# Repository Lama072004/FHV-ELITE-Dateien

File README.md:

# FHV-ELITE
 
Alle Dateien vom Elektronik und Informationstechnologie Studium

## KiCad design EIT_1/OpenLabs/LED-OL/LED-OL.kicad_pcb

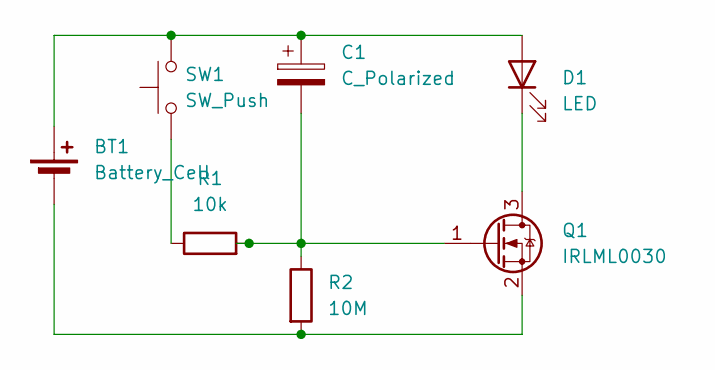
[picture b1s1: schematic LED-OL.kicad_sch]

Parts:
BT1: Battery_Cell; BatteryHolder_Multicomp_BC-2001_1x2032
C1: C_Polarized; C_0603_1608Metric
D1: LED; LED_D1.8mm_W3.3mm_H2.4mm
Q1: IRLML0030; SOT-23
R1: 10k; R_0603_1608Metric
R2: 10M; R_0603_1608Metric
SW1: SW_Push; SW_Push_SPST_NO_Alps_SKRK

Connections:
unnamed: BT1.1 (+), C1.1, D1.2 (A), SW1.2
unnamed: BT1.2 (-), Q1.2 (S), R2.2
unnamed: D1.1 (K), Q1.3 (D)
unnamed: C1.2, Q1.1 (G), R1.2, R2.1
unnamed: R1.1, SW1.1

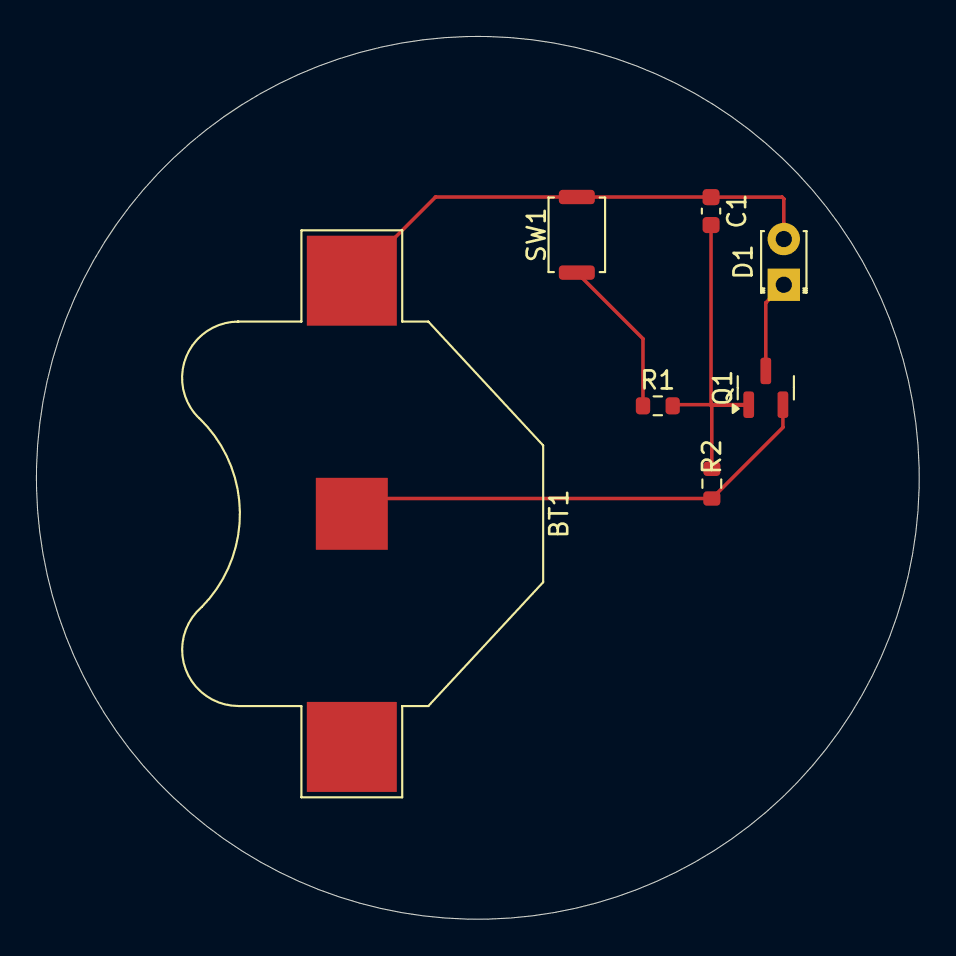
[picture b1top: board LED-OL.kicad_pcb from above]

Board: 2 copper layers, 49.0 x 49.0 mm, 7 parts (0 on the bottom side), 5 nets.

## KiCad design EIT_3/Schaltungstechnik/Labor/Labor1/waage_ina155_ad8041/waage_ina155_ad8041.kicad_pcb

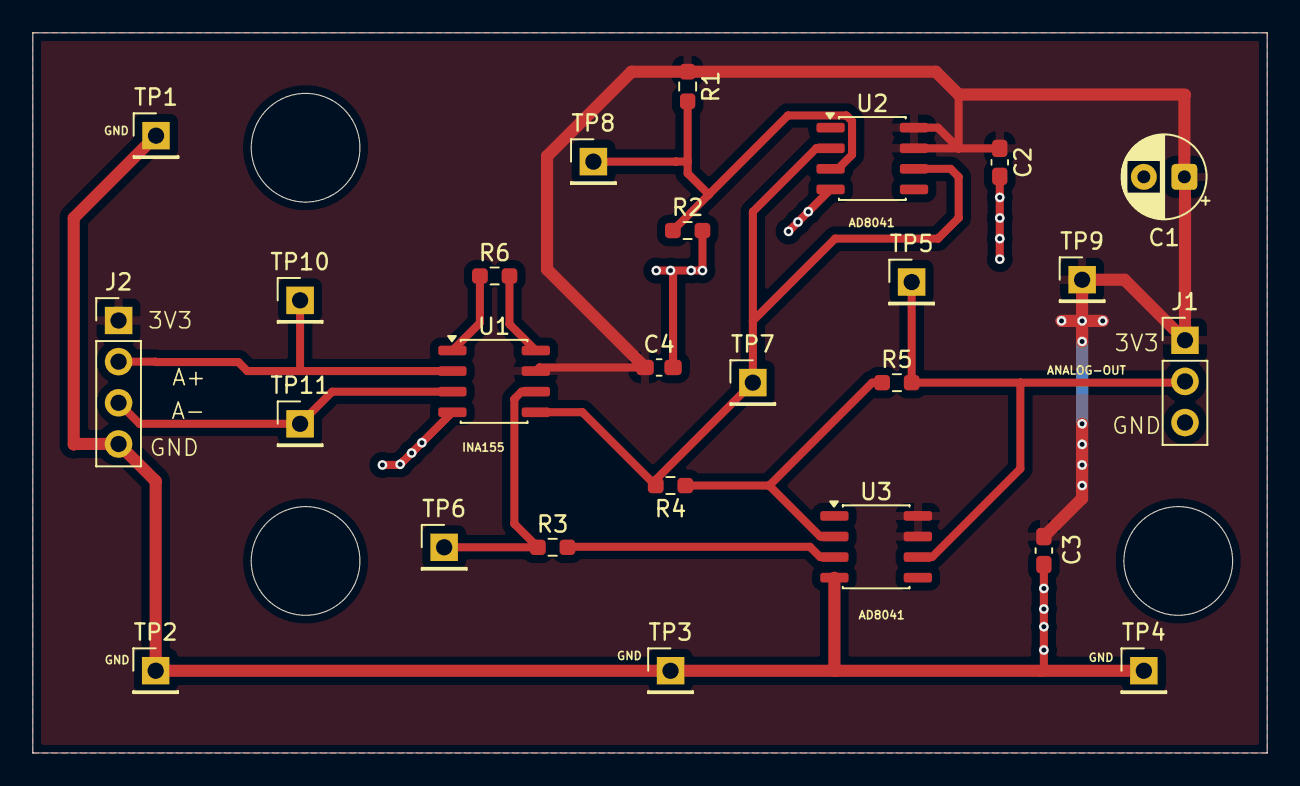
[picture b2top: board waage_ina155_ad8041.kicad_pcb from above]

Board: 2 copper layers, 76.2 x 44.4 mm, 26 parts (0 on the bottom side), 12 nets.

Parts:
C1: 10u; CP_Radial_D5.0mm_P2.50mm
C2, C3, C4: 100n; C_0603_1608Metric_Pad1.08x0.95mm_HandSolder
J1: Conn_01x03_Pin; PinHeader_1x03_P2.54mm_Vertical
J2: Conn_01x04_Pin; PinHeader_1x04_P2.54mm_Vertical
R1, R2, R4: 1k; R_0603_1608Metric_Pad0.98x0.95mm_HandSolder
R3: 500; R_0603_1608Metric_Pad0.98x0.95mm_HandSolder
R5: 9k; R_0603_1608Metric_Pad0.98x0.95mm_HandSolder
R6: R; R_0603_1608Metric_Pad0.98x0.95mm_HandSolder
TP1, TP2, TP3, TP4, TP5, TP6, TP7, TP8, TP9, TP10, TP11: TestPoint; PinHeader_1x01_P2.54mm_Vertical
U1, U2, U3: SO-8_3.9x4.9mm_P1.27mm

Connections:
+3V3: C1.1, C2.1, C3.1, C4.1, J1.1, J2.1, R1.1, TP9.1, U1.7 (V+), U2.7 (+VS), U2.8 (DISABLE), U3.7 (+VS), U3.8 (DISABLE)
/AnalogData: J1.2, R5.2, TP5.1, U3.6 (Output)
/a+: J2.2, TP10.1, U1.2 (Vin-)
/a-: J2.3, TP11.1, U1.3 (Vin+)
GND: C1.2, C2.2, C3.2, C4.2, J1.3, J2.4, R2.2, TP1.1, TP2.1, TP3.1, TP4.1, U1.4 (V-), U2.4 (-VS), U3.4 (-VS)
unnamed: R6.1, U1.1 (RG)
unnamed: R6.2, U1.8 (RG)
unnamed: R4.2, TP7.1, U1.5 (Ref), U2.2 (-Input), U2.6 (Output)
unnamed: R3.1, TP6.1, U1.6 (Vout)
unnamed: R1.2, R2.1, TP8.1, U2.3 (+Input)
unnamed: R3.2, U3.3 (+Input)
unnamed: R4.1, R5.1, U3.2 (-Input)

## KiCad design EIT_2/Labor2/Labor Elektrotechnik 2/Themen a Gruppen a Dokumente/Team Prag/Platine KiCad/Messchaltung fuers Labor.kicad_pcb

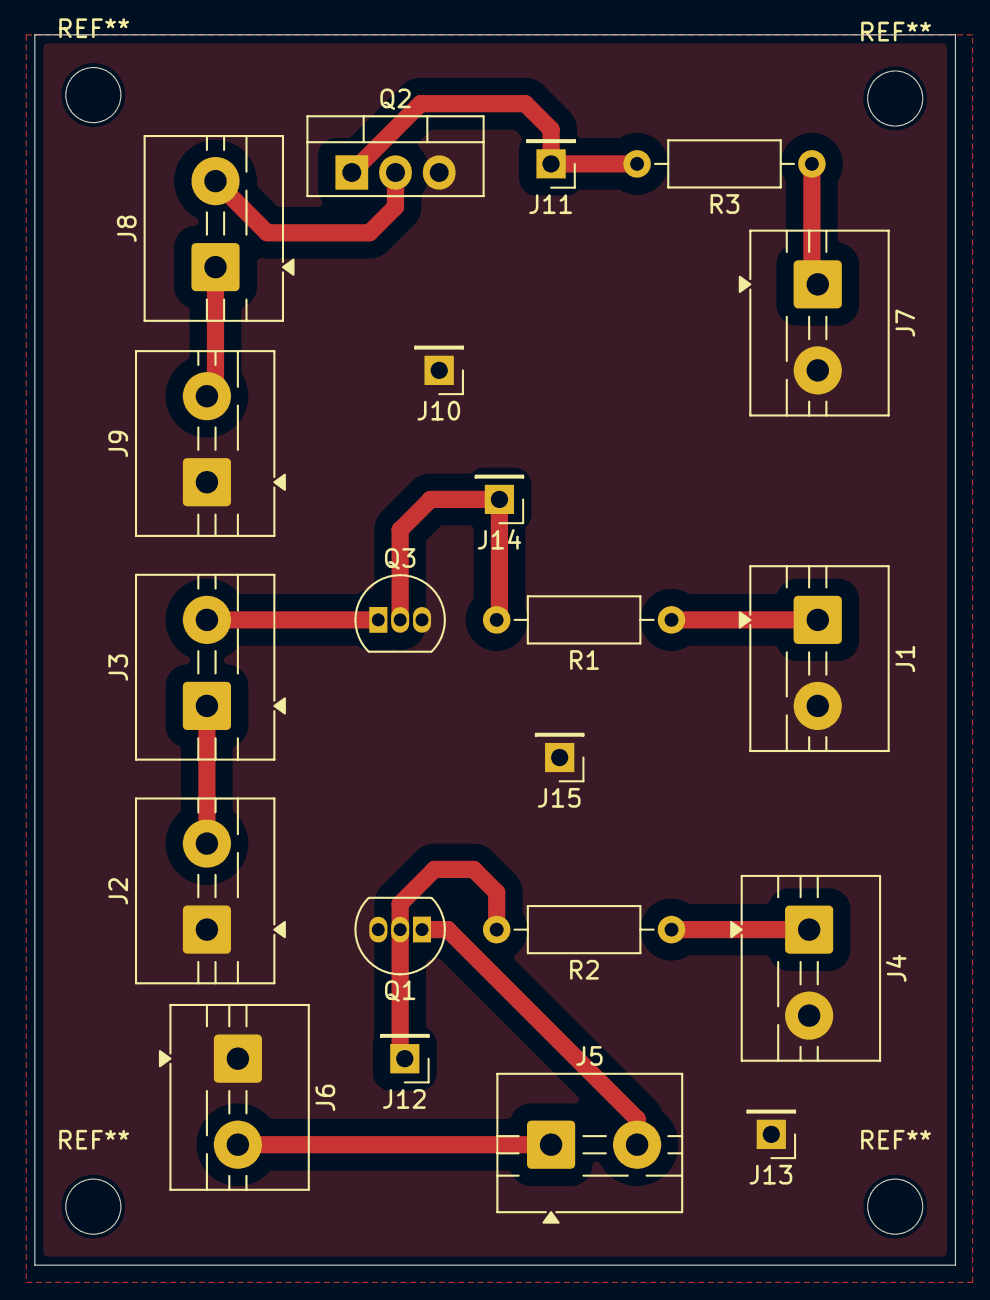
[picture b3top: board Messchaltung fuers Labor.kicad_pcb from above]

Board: 2 copper layers, 53.5 x 71.5 mm, 21 parts (0 on the bottom side), 13 nets.

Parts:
J1, J4, J7: Eingang; TerminalBlock_MaiXu_MX126-5.0-02P_1x02_P5.00mm
J2, J6, J9: Ausgang Schalten; TerminalBlock_MaiXu_MX126-5.0-02P_1x02_P5.00mm
J3, J5, J8: Elektronische Last; TerminalBlock_MaiXu_MX126-5.0-02P_1x02_P5.00mm
J10, J11, J12, J13, J14: Conn_01x01_Pin; PinHeader_1x01_P2.54mm_Vertical
J15: GND; PinHeader_1x01_P2.54mm_Vertical
Q1: BC560; TO-92_Inline
Q2: IRF9530; TO-220-3_Vertical
Q3: BC337; TO-92_Inline
R1, R2, R3: 100; R_Axial_DIN0207_L6.3mm_D2.5mm_P10.16mm_Horizontal

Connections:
GND: J1.2, J2.1, J4.2, J6.1, J7.2, J9.1, J10.1, J13.1, J15.1, Q1.3 (E), Q2.3 (S), Q3.3 (E)
unnamed: J1.1, R1.1
unnamed: J2.2, J3.1
unnamed: J3.2, Q3.1 (C)
unnamed: J4.1, R2.1
unnamed: J5.1, J6.2
unnamed: J5.2, Q1.1 (C)
unnamed: J7.1, R3.1
unnamed: J8.1, J9.2
unnamed: J8.2, Q2.2 (D)
unnamed: J11.1, Q2.1 (G), R3.2
unnamed: J12.1, Q1.2 (B), R2.2
unnamed: J14.1, Q3.2 (B), R1.2

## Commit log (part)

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2025-12-15 Auto-Update Laptop 2025-12-15 13:48
2025-12-15 Auto-Update PC-zuhause 2025-12-15 14:00
2025-12-15 Auto-Update Laptop 2025-12-15 14:02
2025-12-15 Auto-Update PC-zuhause 2025-12-15 14:15
2025-12-15 Auto-Update Laptop 2025-12-15 14:17
2025-12-15 Auto-Update PC-zuhause 2025-12-15 14:30
2025-12-15 Auto-Update Laptop 2025-12-15 14:32
2025-12-15 Auto-Update PC-zuhause 2025-12-15 14:45
2025-12-15 Auto-Update Laptop 2025-12-15 14:47
2025-12-15 Auto-Update PC-zuhause 2025-12-15 15:00
2025-12-15 Auto-Update Laptop 2025-12-15 15:02
2025-12-15 Auto-Update PC-zuhause 2025-12-15 15:15
2025-12-15 Auto-Update Laptop 2025-12-15 15:17
2025-12-15 Auto-Update PC-zuhause 2025-12-15 15:30
2025-12-15 Auto-Update Laptop 2025-12-15 15:32
2025-12-15 Auto-Update PC-zuhause 2025-12-15 15:45
2025-12-15 Auto-Update PC-zuhause 2025-12-15 16:00
2025-12-15 Auto-Update PC-zuhause 2025-12-15 16:15
2025-12-15 Auto-Update PC-zuhause 2025-12-15 16:30
2025-12-15 Auto-Update PC-zuhause 2025-12-15 16:45
2025-12-15 Auto-Update PC-zuhause 2025-12-15 17:00
2025-12-15 Auto-Update PC-zuhause 2025-12-15 17:15
2025-12-15 Auto-Update PC-zuhause 2025-12-15 17:30
2025-12-15 Auto-Update PC-zuhause 2025-12-15 17:45
2025-12-15 Auto-Update PC-zuhause 2025-12-15 18:00
2025-12-15 Auto-Update PC-zuhause 2025-12-15 18:15
2025-12-15 Auto-Update PC-zuhause 2025-12-15 18:30
2025-12-15 Auto-Update PC-zuhause 2025-12-15 18:45
2025-12-15 Auto-Update PC-zuhause 2025-12-15 19:00
2025-12-15 Auto-Update PC-zuhause 2025-12-15 19:15
2025-12-15 Auto-Update PC-zuhause 2025-12-15 19:30
2025-12-15 Auto-Update PC-zuhause 2025-12-15 19:45
2025-12-15 Auto-Update PC-zuhause 2025-12-15 20:00
2025-12-15 Auto-Update PC-zuhause 2025-12-15 20:15
2025-12-15 Auto-Update PC-zuhause 2025-12-15 20:30
2025-12-15 Auto-Update PC-zuhause 2025-12-15 20:45
2025-12-15 Auto-Update PC-zuhause 2025-12-15 21:00
2025-12-15 Auto-Update PC-zuhause 2025-12-15 21:15
2025-12-16 Auto-Update PC-zuhause 2025-12-16 09:13
2025-12-16 Auto-Update PC-zuhause 2025-12-16 09:28
2025-12-16 Auto-Update PC-zuhause 2025-12-16 09:43
2025-12-16 Auto-Update PC-zuhause 2025-12-16 09:58
2025-12-16 Auto-Update PC-zuhause 2025-12-16 10:13
2025-12-16 Auto-Update PC-zuhause 2025-12-16 10:28
2025-12-16 Auto-Update Laptop 2025-12-16 10:42
2025-12-16 Auto-Update PC-zuhause 2025-12-16 10:43
2025-12-16 Auto-Update Laptop 2025-12-16 10:56
2025-12-16 Auto-Update PC-zuhause 2025-12-16 10:58
2025-12-16 Auto-Update PC-zuhause 2025-12-16 11:13
2025-12-16 Auto-Update Laptop 2025-12-16 11:24
2025-12-16 Auto-Update PC-zuhause 2025-12-16 11:28
2025-12-16 Auto-Update Laptop 2025-12-16 11:40
2025-12-16 Auto-Update PC-zuhause 2025-12-16 11:43
2025-12-16 Auto-Update Laptop 2025-12-16 11:55
2025-12-16 Auto-Update PC-zuhause 2025-12-16 11:58
2025-12-16 Auto-Update Laptop 2025-12-16 12:10
2025-12-16 Auto-Update PC-zuhause 2025-12-16 12:13
2025-12-16 Auto-Update Laptop 2025-12-16 12:25
2025-12-16 Auto-Update PC-zuhause 2025-12-16 12:28
2025-12-16 Auto-Update Laptop 2025-12-16 12:39
2025-12-16 Auto-Update PC-zuhause 2025-12-16 12:43
2025-12-16 Auto-Update PC-zuhause 2025-12-16 12:58
2025-12-16 Auto-Update Laptop 2025-12-16 13:05
2025-12-16 Auto-Update PC-zuhause 2025-12-16 13:13
2025-12-16 Auto-Update PC-zuhause 2025-12-16 13:28
2025-12-16 Auto-Update PC-zuhause 2025-12-16 13:43
2025-12-16 Auto-Update PC-zuhause 2025-12-16 13:58
2025-12-16 Auto-Update PC-zuhause 2025-12-16 14:13
2025-12-16 Auto-Update PC-zuhause 2025-12-16 14:28
2025-12-16 Auto-Update PC-zuhause 2025-12-16 14:43
2025-12-16 Auto-Update PC-zuhause 2025-12-16 14:58
2025-12-16 Auto-Update PC-zuhause 2025-12-16 15:13
2025-12-16 Auto-Update PC-zuhause 2025-12-16 15:28
2025-12-16 Auto-Update PC-zuhause 2025-12-16 15:43
2025-12-16 Auto-Update PC-zuhause 2025-12-16 15:58
2025-12-16 Auto-Update PC-zuhause 2025-12-16 16:13
2025-12-16 Auto-Update PC-zuhause 2025-12-16 16:28
2025-12-16 Auto-Update PC-zuhause 2025-12-16 16:43
2025-12-16 Auto-Update PC-zuhause 2025-12-16 16:58
2025-12-16 Auto-Update PC-zuhause 2025-12-16 17:13
2025-12-16 Auto-Update PC-zuhause 2025-12-16 17:28
2025-12-16 Auto-Update PC-zuhause 2025-12-16 17:43
2025-12-16 Auto-Update PC-zuhause 2025-12-16 17:58
2025-12-16 Auto-Update PC-zuhause 2025-12-16 18:13
2025-12-16 Auto-Update PC-zuhause 2025-12-16 18:28
2025-12-16 Auto-Update PC-zuhause 2025-12-16 18:43
2025-12-16 Auto-Update PC-zuhause 2025-12-16 18:58
2025-12-16 Auto-Update PC-zuhause 2025-12-16 19:13
2025-12-16 Auto-Update PC-zuhause 2025-12-16 19:28
2025-12-16 Auto-Update PC-zuhause 2025-12-16 19:43
2025-12-16 Auto-Update PC-zuhause 2025-12-16 19:58
2025-12-16 Auto-Update PC-zuhause 2025-12-16 20:13
2025-12-16 Auto-Update PC-zuhause 2025-12-16 20:28
2025-12-16 Auto-Update PC-zuhause 2025-12-16 20:43
2025-12-16 Auto-Update PC-zuhause 2025-12-16 20:58
2025-12-16 Auto-Update PC-zuhause 2025-12-16 21:13
2025-12-16 Auto-Update PC-zuhause 2025-12-16 21:28
2025-12-16 Auto-Update PC-zuhause 2025-12-16 21:43
2025-12-16 Auto-Update PC-zuhause 2025-12-16 21:58
2025-12-16 Auto-Update PC-zuhause 2025-12-16 22:13
2025-12-16 Auto-Update PC-zuhause 2025-12-16 22:28
2025-12-16 Auto-Update PC-zuhause 2025-12-16 22:43
2025-12-16 Auto-Update PC-zuhause 2025-12-16 22:58
2025-12-17 Auto-Update PC-zuhause 2025-12-17 10:18
2025-12-17 Auto-Update PC-zuhause 2025-12-15 12:30
2025-12-17 schaltungstechnik
2025-12-20 20.12.2025
2025-12-21 Auto-Update PC-zuhause 2025-12-21 16:50
2026-03-25 25.03.2026
2026-03-28 28.03.2026
2026-04-03 systemprogrammieren latex altprüfung
2026-04-03 jfkd
2026-04-06 06.04
2026-04-08 08.04
2026-04-09 statistik
2026-04-15 15.04
2026-04-15 Zukunft des fliegens
2026-04-15 arbeit
2026-04-16 wahrscheinlichkeitsrechnung
2026-04-17 wahrscheinlichkeit
2026-04-19 wahrsch
2026-04-20 digitaltechnik und auslandsemester
2026-04-21 21042026
2026-04-22 digitaltechnik
2026-04-22 formelheft-emf
2026-04-22 latex digitaltechnik labor
2026-04-22 Digitaltechnik labor bericht latex
2026-04-26 Laborprotokoll Digitaltechnik
2026-04-29 lab02
2026-04-30 formelheft
2026-04-30 labor 2 digitaltechnik
2026-05-05 05.05.2026
2026-05-12 12.05.2026
2026-05-12 12.05.2026_2
2026-05-12 12-05-2026
2026-05-13 13052026
2026-05-13 13.05.2026
2026-05-13 Sensorik
2026-05-18 18.05.2026
2026-05-20 20.05.2026
2026-05-26 26.05.2026
2026-05-26 sensorik messchaltung projekt
2026-05-26 Projekt sensorik und messchaltungen
2026-05-29 29.05.2026
2026-05-29 Zusammenfassung Sensorik und Messchaltungen + Signalverarbeitung
2026-06-01 01.06.2026
2026-06-02 projekt überarbeitet
2026-06-10 10.06.2026
2026-06-11 Signalverarbeitung
2026-06-12 12.06.20026
2026-06-17 17.06.2026
2026-06-22 22.06.2026
2026-06-22 22062026
2026-06-22 speichersysteme
2026-06-26 26062026
2026-06-29 29.06.2026
